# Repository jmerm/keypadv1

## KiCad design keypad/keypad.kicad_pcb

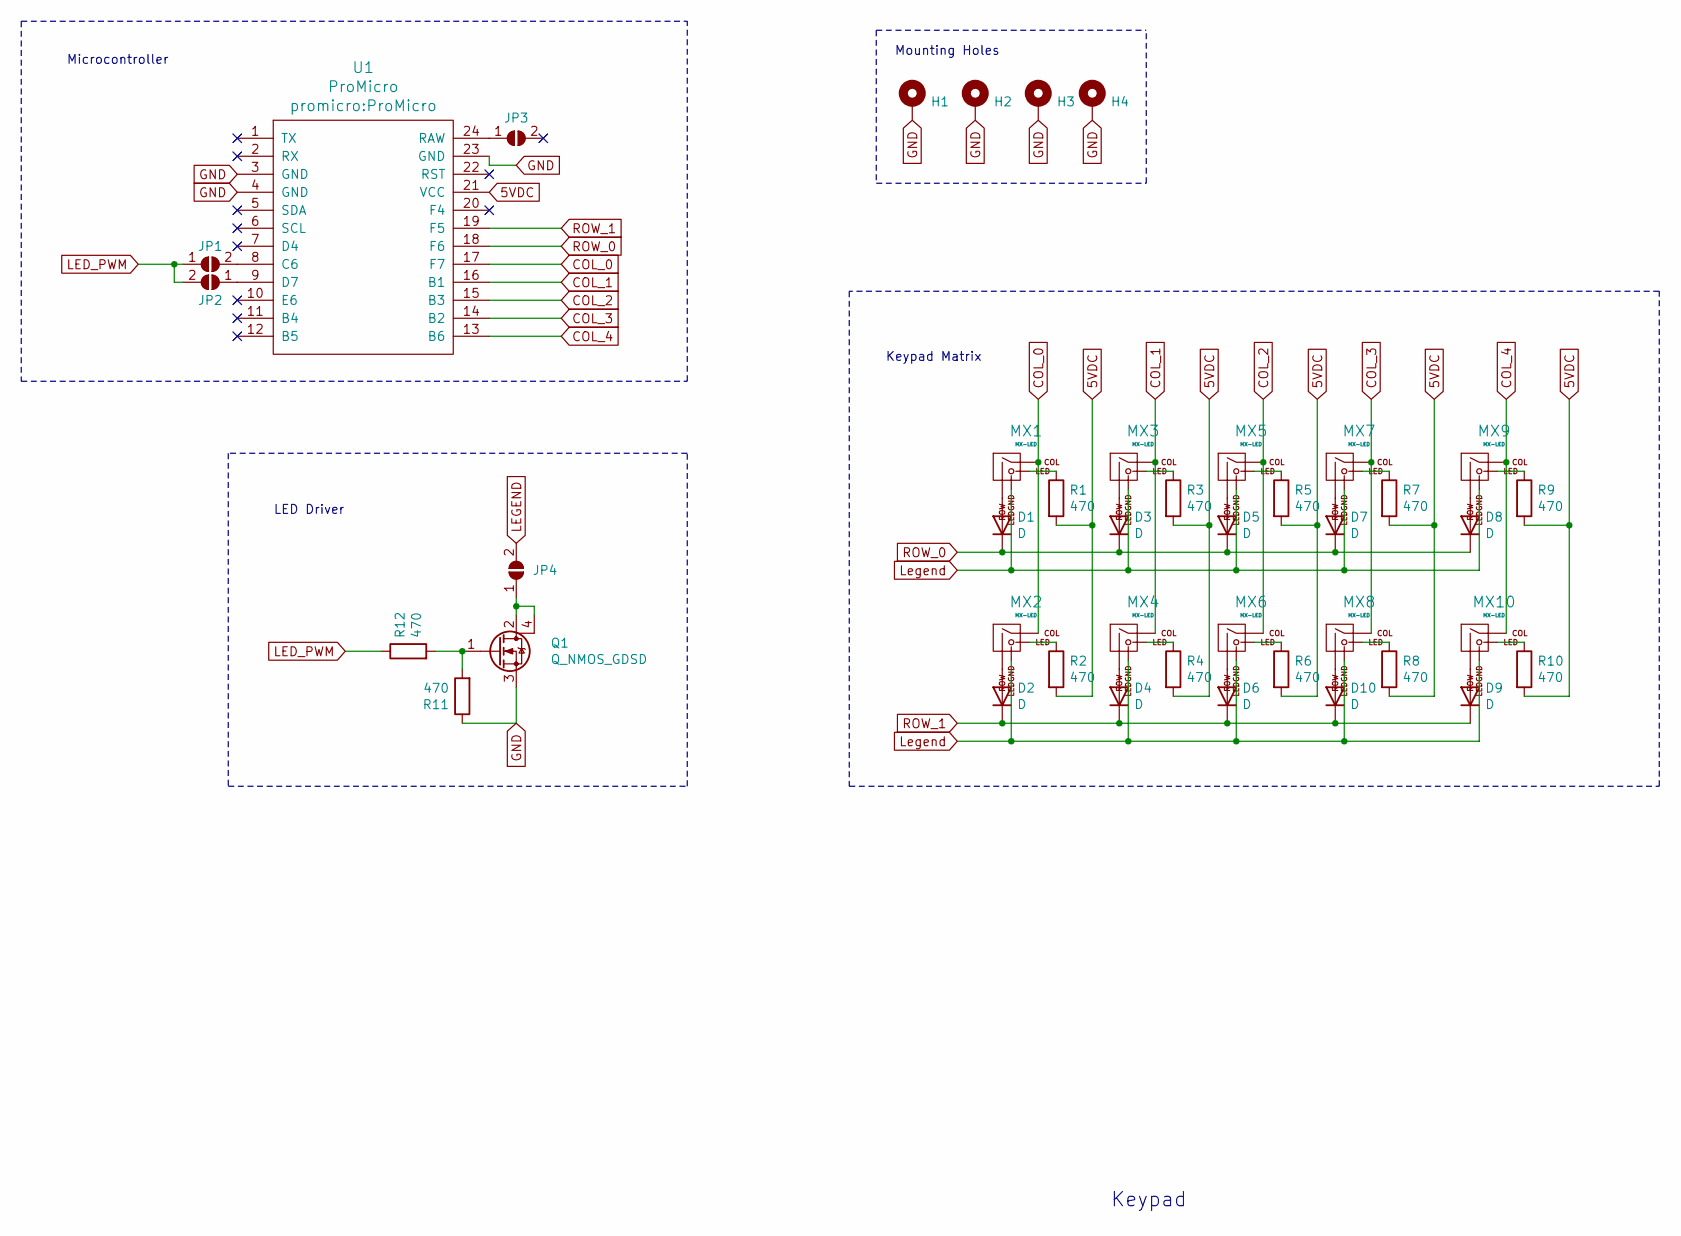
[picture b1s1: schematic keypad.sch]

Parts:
D1, D2, D3, D4, D5, D6, D7, D8, D9, D10: D; D_SOT-23_ANK
H1, H2, H3, H4: MountingHole_Pad; MountingHole_3.2mm_M3
JP1, JP2, JP3, JP4: SolderJumper_2_Open; SolderJumper-2_P1.3mm_Open_RoundedPad1.0x1.5mm
MX1, MX2, MX3, MX4, MX5, MX6, MX7, MX8, MX9, MX10: MX-LED; MXOnly-1U
Q1: Q_NMOS_GDSD; SOT-223
R1, R2, R3, R4, R5, R6, R7, R8, R9, R10, R11, R12: 470; R_0805_2012Metric
U1: ProMicro

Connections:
5VDC: R1.2, R2.2, R3.2, R4.2, R5.2, R6.2, R7.2, R8.2, R9.2, R10.2, U1.21 (VCC)
COL_0: MX1.1 (COL), MX2.1 (COL), U1.17 (F7)
COL_1: MX3.1 (COL), MX4.1 (COL), U1.16 (B1)
COL_2: MX5.1 (COL), MX6.1 (COL), U1.15 (B3)
COL_3: MX7.1 (COL), MX8.1 (COL), U1.14 (B2)
COL_4: MX9.1 (COL), MX10.1 (COL), U1.13 (B6)
GND: H1.1, H2.1, H3.1, H4.1, Q1.3 (S), R11.1, U1.3 (GND), U1.4 (GND), U1.23 (GND)
LED_PWM: JP1.1 (A), JP2.2 (B), R12.1
LEGEND: JP4.2 (B)
Legend: MX1.4 (LEDGND), MX2.4 (LEDGND), MX3.4 (LEDGND), MX4.4 (LEDGND), MX5.4 (LEDGND), MX6.4 (LEDGND), MX7.4 (LEDGND), MX8.4 (LEDGND), MX9.4 (LEDGND), MX10.4 (LEDGND)
unnamed: D1.2 (A), MX1.2 (ROW)
unnamed: D2.2 (A), MX2.2 (ROW)
unnamed: D3.2 (A), MX3.2 (ROW)
unnamed: D4.2 (A), MX4.2 (ROW)
unnamed: D5.2 (A), MX5.2 (ROW)
unnamed: D6.2 (A), MX6.2 (ROW)
unnamed: D7.2 (A), MX7.2 (ROW)
unnamed: D8.2 (A), MX9.2 (ROW)
unnamed: D9.2 (A), MX10.2 (ROW)
unnamed: D10.2 (A), MX8.2 (ROW)
unnamed: JP1.2 (B), U1.8 (C6)
unnamed: JP2.1 (A), U1.9 (D7)
unnamed: JP3.1 (A), U1.24 (RAW)
unnamed: JP4.1 (A), Q1.2 (D), Q1.4 (D)
unnamed: MX1.3 (LED), R1.1
unnamed: MX2.3 (LED), R2.1
unnamed: MX3.3 (LED), R3.1
unnamed: MX4.3 (LED), R4.1
unnamed: MX5.3 (LED), R5.1
unnamed: MX6.3 (LED), R6.1
unnamed: MX7.3 (LED), R7.1
unnamed: MX8.3 (LED), R8.1
unnamed: MX9.3 (LED), R9.1
unnamed: MX10.3 (LED), R10.1
unnamed: Q1.1 (G), R11.2, R12.2
ROW_0: D1.1 (K), D3.1 (K), D5.1 (K), D7.1 (K), D8.1 (K), U1.18 (F6)
ROW_1: D2.1 (K), D4.1 (K), D6.1 (K), D9.1 (K), D10.1 (K), U1.19 (F5)

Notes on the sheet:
Keypad
Microcontroller
LED Driver
Keypad Matrix
Mounting Holes

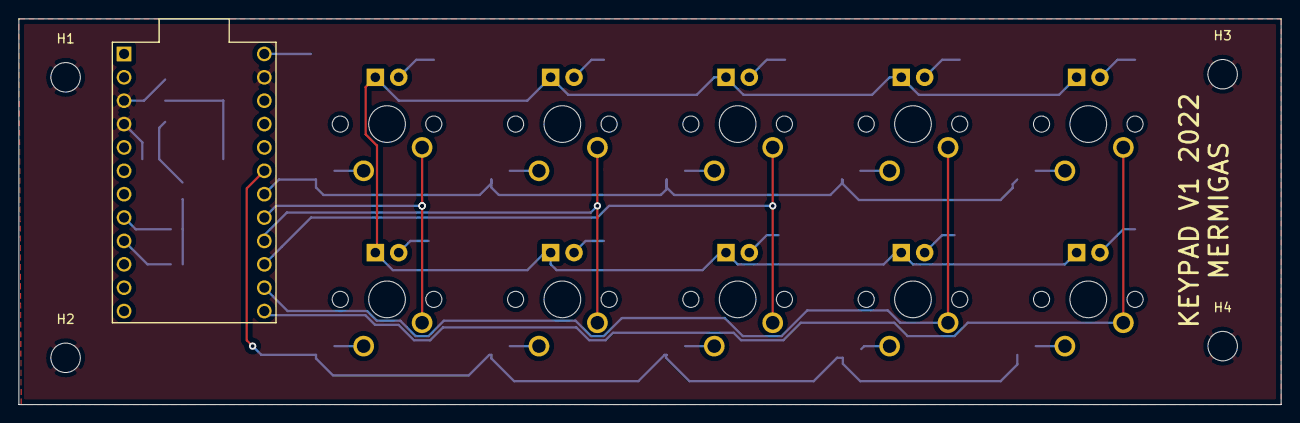
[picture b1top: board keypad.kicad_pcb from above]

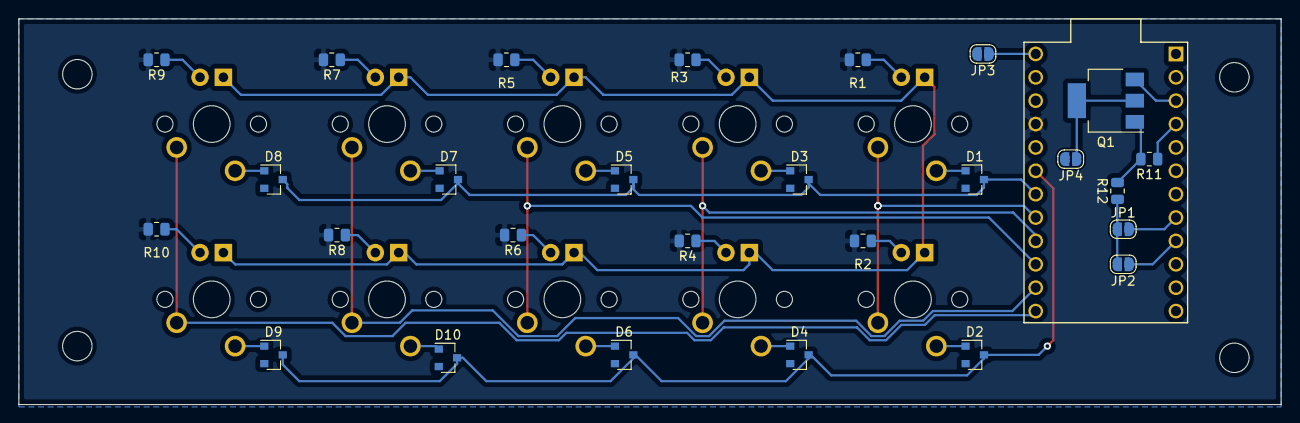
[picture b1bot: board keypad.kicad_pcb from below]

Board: 2 copper layers, 137.2 x 41.9 mm, 42 parts (27 on the bottom side), 36 nets.
